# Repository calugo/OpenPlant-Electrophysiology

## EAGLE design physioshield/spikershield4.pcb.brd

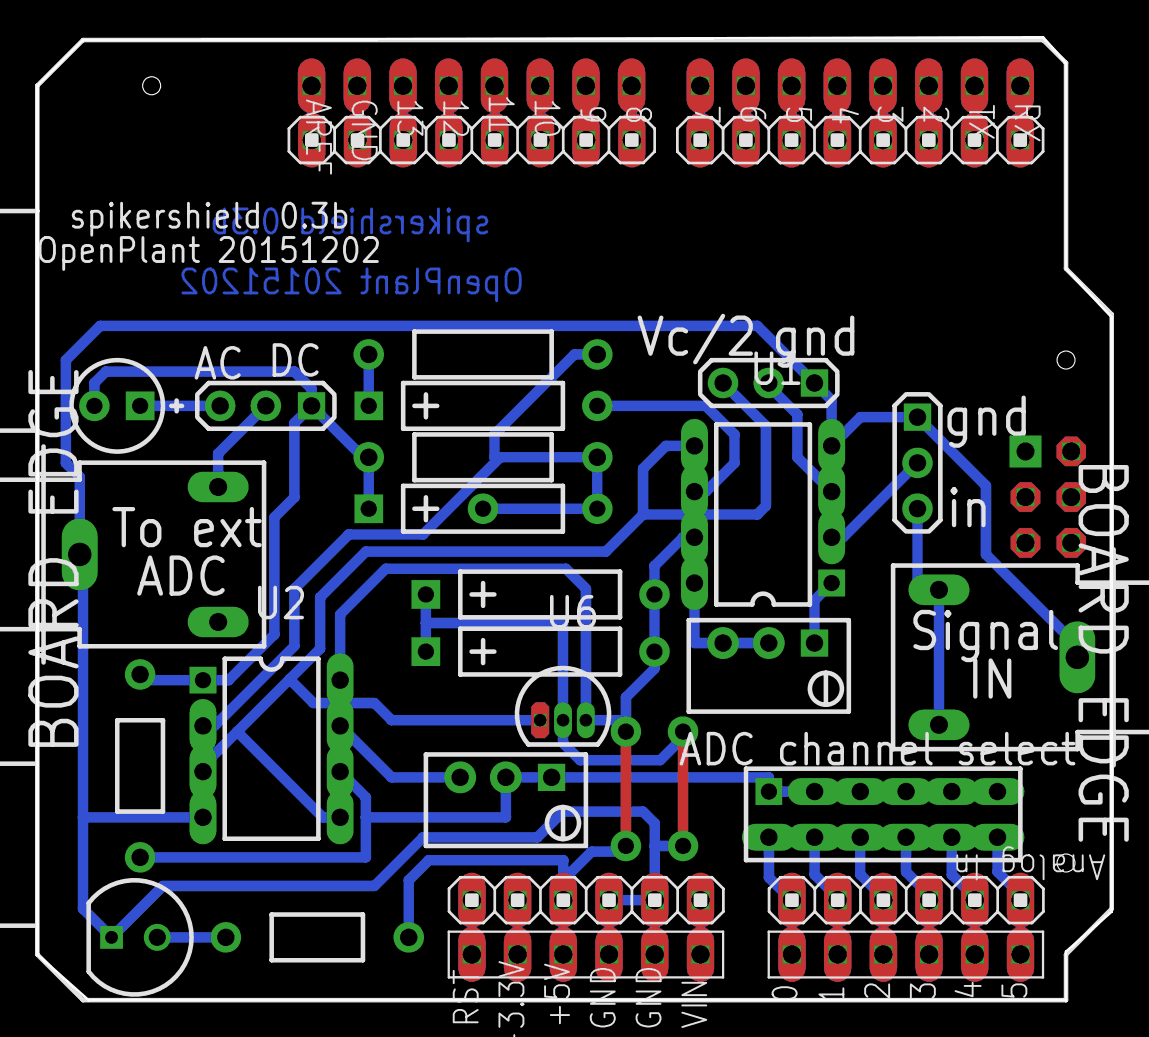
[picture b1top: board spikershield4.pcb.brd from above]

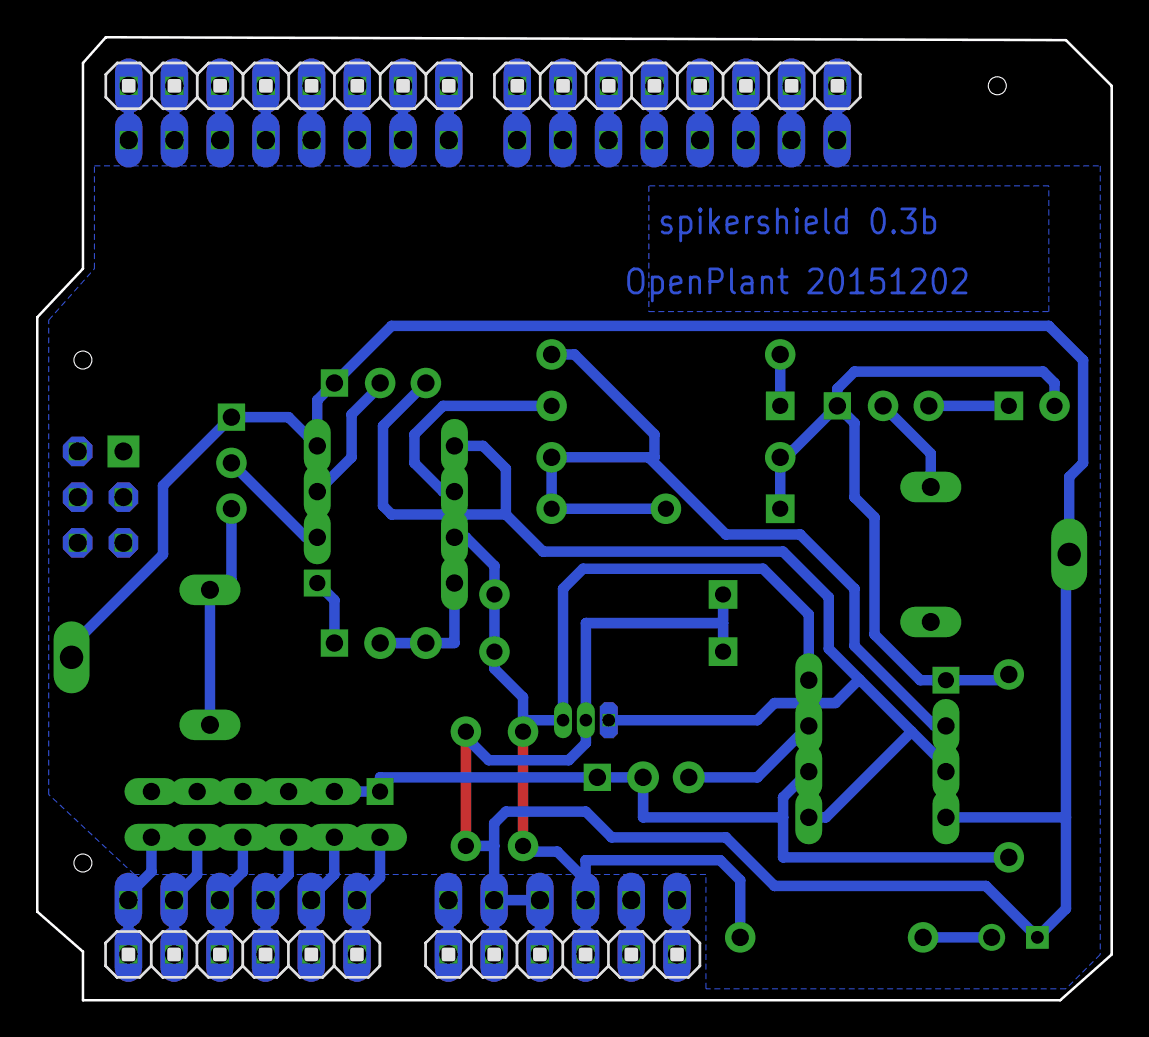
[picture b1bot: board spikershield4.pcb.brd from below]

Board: 2 copper layers, 59.7 x 53.5 mm, 43 parts (8 on the bottom side), 41 nets.

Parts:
C3: 10uF; CAP500AP_0PRIMARY
C4: 360pF; CAP500AP_0PRIMARY
C5: CAP100RP_1PRIMARY
C6: 1uF; CAP500AP_0PRIMARY
C7: 10nF; CAP500AP_0PRIMARY
D1: LED_2PRIMARY
HOLE1: COMP_3PRIMARY
HOLE2: COMP_4PRIMARY
HOLE3: COMP_5PRIMARY
J1, J6, J7, J12: 1X08_6PRIMARY
J2, J5, J11: JUMPER_3_7PRIMARY
J3, J4: RCA_JACK_8PRIMARY
J8, J9, J13: 1X06_9PRIMARY
PAD1: COMP_10PRIMARY
PAD2: COMP_11PRIMARY
PAD3: COMP_12PRIMARY
PAD4: COMP_13PRIMARY
PAD5: COMP_14PRIMARY
PAD6: COMP_15PRIMARY
PAD19, PAD20, PAD21, PAD22, PAD23: PAD_16PRIMARY
POWER1: 1X06_17PRIMARY
R1: POT3T_18PRIMARY
R2: 390; RES400_19PRIMARY
R5: 2.2M; RES500_20PRIMARY
R6: 100k; RES500_21PRIMARY
R7: 1k; RES400_19PRIMARY
R8: 5k; POT3T_18PRIMARY
U1: AD623AN_22PRIMARY
U2: AD623AN_23PRIMARY
U4: HDR-2X6_24PRIMARY
U6: TLE2426*LP_25PRIMARY

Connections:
NET_0: C6.2, C7.2, D1.2, J2.1, J3.1, J4.1, J5.1, J9.2, J9.3, PAD21.1, PAD22.1, POWER1.4, POWER1.5, U1.4, U2.4, U6.2
NET_1: J2.2, U1.3
NET_2: D1.1, R2.2
NET_3: J2.3, U1.5, U2.3, U2.5, U6.1
NET_4: R1.1, R1.2, R1.3, U1.1, U1.8
NET_5: R8.3, U2.7
NET_6: R7.1, R8.1, R8.2, U2.6, U4.1, U4.3, U4.5, U4.7, U4.9, U4.11
NET_7: J3.2, J3.3, J5.3
NET_8: J5.2, U1.2
NET_9: C3.1, U1.6
NET_10: C6.1, C7.1, J9.4, PAD19.1, PAD20.1, POWER1.3, R2.1, U1.7, U2.8, U6.3
NET_11: C4.1, PAD23.1, R5.1, R6.1, U2.2
NET_12: J1.6, J12.3
NET_13: J8.6, J13.1, U4.2
NET_14: J6.2, J7.7
NET_15: J8.5, J13.2, U4.4
NET_16: J8.4, J13.3, U4.6
NET_17: J8.3, J13.4, U4.8
NET_18: J8.2, J13.5, U4.10
NET_19: J9.6, POWER1.1
NET_20: J9.5, POWER1.2
NET_21: J9.1, POWER1.6
NET_22: J8.1, J13.6, U4.12
NET_23: J4.2, J11.2
NET_24: C4.2, C5.2, J11.1, R5.2, R7.2, U2.1
NET_25: J1.8, J12.1
NET_26: J1.7, J12.2
NET_27: C3.2, R6.2
NET_28: J1.5, J12.4
NET_29: J1.4, J12.5
NET_30: J1.3, J12.6
NET_31: J1.2, J12.7
NET_32: J1.1, J12.8
NET_33: J6.8, J7.1
NET_34: J6.7, J7.2
NET_35: J6.6, J7.3
NET_36: J6.5, J7.4
NET_37: J6.4, J7.5
NET_38: J6.3, J7.6
NET_39: C5.1, J11.3
NET_40: J6.1, J7.8

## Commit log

2016-04-23 OpenPlantRep
2016-05-10 Octopress init
2016-05-10 Site updated at 2016-05-10 01:56:22 UTC
2016-05-10 Site updated at 2016-05-10 02:11:50 UTC
2016-05-10 Site updated at 2016-05-10 02:36:09 UTC
2016-05-10 Site updated at 2016-05-10 02:48:09 UTC
2016-05-10 Site updated at 2016-05-10 03:03:58 UTC
2016-05-10 Site updated at 2016-05-10 03:08:27 UTC
2016-05-10 Site updated at 2016-05-10 03:09:11 UTC
2016-05-10 Site updated at 2016-05-10 03:11:01 UTC
2016-05-10 Site updated at 2016-05-10 03:13:34 UTC
2016-05-10 Site updated at 2016-05-10 03:14:57 UTC
2016-05-10 Site updated at 2016-05-10 09:36:06 UTC
2016-05-10 lorenz add
2016-05-10 Site updated at 2016-05-10 21:52:58 UTC
2016-05-10 Site updated at 2016-05-10 21:57:38 UTC
2017-01-16 Playstation2 controller for three motors
    Allows to use a Playstation 2 controller to control three stepper
    motors. Used to control the x,y,z, axis of the micromanipulator.
2017-01-16 minimal change, to test Github system
    No functional changes. TODO introduce delay in stepsize controls and see
    if it works better (now need to press another control before a further
    change in stepsize is allowed).
2017-02-14 Site updated at 2017-02-14 04:15:48 UTC
2017-02-14 Site updated at 2017-02-14 04:46:56 UTC
2017-02-14 test
2017-02-14 Site updated at 2017-02-14 04:57:39 UTC
2017-02-14 Site updated at 2017-02-14 05:09:57 UTC
2017-02-14 Site updated at 2017-02-14 05:13:23 UTC
2017-02-14 Site updated at 2017-02-14 05:31:54 UTC
2017-02-14 Site updated at 2017-02-14 05:33:24 UTC
2017-02-14 Site updated at 2017-02-14 05:40:42 UTC
2017-02-14 Site updated at 2017-02-14 05:42:19 UTC
2017-02-14 Site updated at 2017-02-14 05:44:29 UTC
2017-02-14 Site updated at 2017-02-14 05:46:47 UTC
2017-02-14 Site updated at 2017-02-14 05:49:13 UTC
2017-02-14 Site updated at 2017-02-14 05:52:55 UTC
2017-02-14 Site updated at 2017-02-14 05:56:26 UTC
2017-02-14 Site updated at 2017-02-14 06:10:15 UTC
2017-02-14 Site updated at 2017-02-14 06:16:32 UTC
2017-02-14 Site updated at 2017-02-14 07:42:41 UTC
2017-02-14 Site updated at 2017-02-14 07:44:44 UTC
2017-02-14 Site updated at 2017-02-14 07:46:56 UTC
2017-02-14 Site updated at 2017-02-14 07:48:56 UTC
2017-02-14 Site updated at 2017-02-14 07:50:29 UTC
2017-02-14 Site updated at 2017-02-14 07:51:40 UTC
2017-02-14 Site updated at 2017-02-14 07:54:22 UTC
2017-02-14 Site updated at 2017-02-14 07:56:48 UTC
2017-02-14 Site updated at 2017-02-14 08:02:03 UTC
2017-02-14 Site updated at 2017-02-14 08:04:37 UTC
2017-02-14 Site updated at 2017-02-14 08:07:48 UTC
2017-02-14 Site updated at 2017-02-14 08:09:38 UTC
2017-02-14 Site updated at 2017-02-14 08:11:28 UTC
2017-02-14 Site updated at 2017-02-14 08:14:09 UTC
2017-02-14 Site updated at 2017-02-14 08:15:57 UTC
2017-02-14 Site updated at 2017-02-14 08:17:51 UTC
2017-02-14 Site updated at 2017-02-14 08:20:51 UTC
2017-02-14 Site updated at 2017-02-14 08:22:36 UTC
2017-02-14 Site updated at 2017-02-14 08:24:42 UTC
2017-02-14 Site updated at 2017-02-14 08:26:59 UTC
2017-02-14 Site updated at 2017-02-14 08:32:51 UTC
2017-02-14 Site updated at 2017-02-14 08:34:17 UTC
2017-02-14 Site updated at 2017-02-14 08:35:54 UTC
2017-02-14 Site updated at 2017-02-14 08:37:19 UTC
2017-02-14 Site updated at 2017-02-14 13:37:14 UTC
2017-02-14 Site updated at 2017-02-14 13:41:53 UTC
2017-02-14 Site updated at 2017-02-14 15:05:26 UTC
2017-02-14 Site updated at 2017-02-14 15:06:19 UTC
2017-02-14 Site updated at 2017-02-14 16:40:05 UTC
2017-02-15 Site updated at 2017-02-15 03:42:53 UTC
2017-02-15 Site updated at 2017-02-15 03:44:30 UTC
2017-02-15 Site updated at 2017-02-15 03:46:16 UTC
2017-02-15 Site updated at 2017-02-15 03:47:54 UTC
2017-02-15 Site updated at 2017-02-15 03:56:43 UTC
2017-02-15 Site updated at 2017-02-15 03:58:04 UTC
2017-02-15 Site updated at 2017-02-15 04:00:51 UTC
2017-02-15 Site updated at 2017-02-15 04:07:28 UTC
2017-02-15 Site updated at 2017-02-15 04:14:56 UTC
2017-02-15 Site updated at 2017-02-15 04:44:24 UTC
2017-02-15 Site updated at 2017-02-15 04:47:06 UTC
2017-02-15 Site updated at 2017-02-15 14:10:15 UTC
2017-02-15 Site updated at 2017-02-15 14:12:56 UTC
2017-02-15 Site updated at 2017-02-15 14:20:26 UTC
2017-02-15 Site updated at 2017-02-15 14:39:18 UTC
2017-02-15 Site updated at 2017-02-15 14:40:04 UTC
2017-02-15 Site updated at 2017-02-15 14:46:02 UTC
2017-02-15 Site updated at 2017-02-15 14:52:25 UTC
2017-02-15 Site updated at 2017-02-15 14:56:26 UTC
2017-02-15 Site updated at 2017-02-15 14:58:45 UTC
2017-02-15 Site updated at 2017-02-15 14:59:58 UTC
2017-02-15 Site updated at 2017-02-15 15:02:15 UTC
2017-02-15 Site updated at 2017-02-15 15:04:27 UTC
2017-02-15 Site updated at 2017-02-15 15:05:49 UTC
2017-02-15 Site updated at 2017-02-15 23:21:21 UTC
2017-02-15 Site updated at 2017-02-15 23:23:53 UTC
2017-02-15 Site updated at 2017-02-15 23:26:04 UTC
2017-02-15 Site updated at 2017-02-15 23:33:58 UTC
2017-02-15 Site updated at 2017-02-15 23:42:59 UTC
2017-02-15 Site updated at 2017-02-15 23:46:17 UTC
2017-02-15 Site updated at 2017-02-15 23:51:36 UTC
2017-02-15 Site updated at 2017-02-15 23:52:30 UTC
2017-02-16 Site updated at 2017-02-16 00:15:22 UTC
2017-02-16 Site updated at 2017-02-16 00:21:45 UTC
2017-02-16 Site updated at 2017-02-16 00:32:09 UTC
2017-02-16 Site updated at 2017-02-16 00:36:41 UTC
2017-02-16 Site updated at 2017-02-16 00:44:48 UTC
2017-02-16 Site updated at 2017-02-16 00:49:31 UTC
2017-02-16 Site updated at 2017-02-16 00:57:52 UTC
2017-02-16 Site updated at 2017-02-16 01:00:37 UTC
2017-02-16 Site updated at 2017-02-16 01:04:52 UTC
2017-02-16 Site updated at 2017-02-16 01:21:44 UTC
2017-02-16 Site updated at 2017-02-16 01:28:42 UTC
2017-02-16 Site updated at 2017-02-16 01:59:53 UTC
2017-02-16 Site updated at 2017-02-16 02:06:13 UTC
2017-02-16 Site updated at 2017-02-16 02:21:30 UTC
2017-02-16 Site updated at 2017-02-16 02:27:32 UTC
2017-02-16 Site updated at 2017-02-16 02:29:40 UTC
2017-02-16 Site updated at 2017-02-16 02:32:20 UTC
2017-02-16 Site updated at 2017-02-16 02:33:46 UTC
2017-02-16 Site updated at 2017-02-16 02:35:51 UTC
2017-02-16 Site updated at 2017-02-16 02:39:09 UTC
2017-02-16 Site updated at 2017-02-16 02:40:51 UTC
2017-02-16 Site updated at 2017-02-16 02:42:15 UTC
2017-02-16 Site updated at 2017-02-16 02:44:19 UTC
2017-02-16 Site updated at 2017-02-16 02:49:14 UTC
2017-02-16 Site updated at 2017-02-16 02:56:32 UTC
2017-02-16 Site updated at 2017-02-16 02:58:37 UTC
2017-02-16 Site updated at 2017-02-16 03:21:23 UTC
2017-02-16 Site updated at 2017-02-16 03:27:40 UTC
2017-02-16 Site updated at 2017-02-16 03:32:08 UTC
2017-02-16 Site updated at 2017-02-16 03:37:08 UTC
2017-02-16 Site updated at 2017-02-16 03:44:01 UTC
2017-02-16 Site updated at 2017-02-16 03:45:20 UTC
2017-03-02 Site updated at 2017-03-02 00:22:20 UTC
2017-03-14 Site updated at 2017-03-14 18:26:22 UTC
2017-03-14 Site updated at 2017-03-14 18:29:03 UTC
2017-03-14 Site updated at 2017-03-14 22:36:50 UTC
2017-03-14 Site updated at 2017-03-14 22:56:49 UTC
2017-03-14 Site updated at 2017-03-14 22:57:59 UTC
2017-03-14 Site updated at 2017-03-14 23:16:44 UTC
2017-03-14 Site updated at 2017-03-14 23:20:42 UTC
2017-03-14 Site updated at 2017-03-14 23:24:08 UTC
2017-03-14 Site updated at 2017-03-14 23:26:44 UTC
2017-03-14 Site updated at 2017-03-14 23:28:40 UTC
2017-03-14 Site updated at 2017-03-14 23:34:00 UTC
2017-03-14 Site updated at 2017-03-14 23:35:39 UTC
2017-03-14 Site updated at 2017-03-14 23:40:36 UTC
2017-03-14 Site updated at 2017-03-14 23:43:19 UTC
2017-03-14 Site updated at 2017-03-14 23:46:42 UTC
2017-03-14 Site updated at 2017-03-14 23:54:48 UTC
2017-03-14 Site updated at 2017-03-14 23:59:57 UTC
2017-03-15 Site updated at 2017-03-15 00:04:44 UTC
2017-03-15 Site updated at 2017-03-15 00:07:22 UTC
2017-03-15 Site updated at 2017-03-15 00:14:31 UTC
2017-03-15 Site updated at 2017-03-15 00:19:35 UTC
2017-03-15 Site updated at 2017-03-15 00:49:21 UTC
2017-03-15 Site updated at 2017-03-15 01:05:13 UTC
2017-03-15 Site updated at 2017-03-15 01:13:12 UTC
2017-03-15 Site updated at 2017-03-15 01:17:25 UTC
2017-03-15 Site updated at 2017-03-15 01:41:14 UTC
2017-03-15 Site updated at 2017-03-15 01:43:43 UTC
2017-03-15 Site updated at 2017-03-15 01:49:43 UTC
2017-03-15 Site updated at 2017-03-15 02:03:05 UTC
2017-03-15 Site updated at 2017-03-15 15:57:09 UTC
2017-03-15 Site updated at 2017-03-15 16:32:46 UTC
2017-03-15 Site updated at 2017-03-15 17:33:16 UTC
2017-03-15 Site updated at 2017-03-15 17:52:07 UTC
2017-03-15 Site updated at 2017-03-15 18:17:04 UTC
2017-03-15 Site updated at 2017-03-15 18:19:05 UTC
2017-03-15 Site updated at 2017-03-15 18:21:32 UTC
2017-03-15 Site updated at 2017-03-15 18:24:10 UTC
2017-03-15 Site updated at 2017-03-15 18:27:01 UTC
2017-03-15 Site updated at 2017-03-15 19:47:08 UTC
2017-03-15 Site updated at 2017-03-15 19:51:37 UTC
2017-03-15 Site updated at 2017-03-15 21:07:46 UTC
2017-03-15 Site updated at 2017-03-15 22:42:23 UTC
2017-03-15 Site updated at 2017-03-15 22:47:10 UTC
2017-03-15 Site updated at 2017-03-15 22:51:19 UTC
2017-03-15 Site updated at 2017-03-15 22:53:45 UTC
2017-03-15 Site updated at 2017-03-15 23:00:12 UTC
2017-03-15 Site updated at 2017-03-15 23:02:34 UTC
2017-03-15 Site updated at 2017-03-15 23:15:59 UTC
2017-03-15 Site updated at 2017-03-15 23:19:03 UTC
2017-03-15 Site updated at 2017-03-15 23:24:32 UTC
2017-03-15 Site updated at 2017-03-15 23:34:22 UTC
2017-03-15 Site updated at 2017-03-15 23:36:36 UTC
2017-03-15 Site updated at 2017-03-15 23:39:02 UTC
2017-03-15 Site updated at 2017-03-15 23:41:06 UTC
2017-03-16 Site updated at 2017-03-16 00:17:25 UTC
2017-03-16 Site updated at 2017-03-16 09:44:17 UTC
2017-03-16 Site updated at 2017-03-16 09:57:58 UTC
2017-03-16 Site updated at 2017-03-16 10:14:18 UTC
2017-03-16 Site updated at 2017-03-16 11:19:08 UTC
2017-03-16 Site updated at 2017-03-16 13:40:12 UTC
2017-03-16 Site updated at 2017-03-16 13:43:47 UTC
2017-03-16 Site updated at 2017-03-16 19:27:31 UTC
2017-03-16 Site updated at 2017-03-16 19:31:15 UTC
2017-03-16 Site updated at 2017-03-16 21:14:04 UTC
2017-03-16 Site updated at 2017-03-16 21:16:55 UTC
2017-03-17 Site updated at 2017-03-17 00:21:59 UTC
2017-03-17 Site updated at 2017-03-17 00:28:09 UTC
2017-03-17 Site updated at 2017-03-17 00:32:03 UTC
2017-03-17 Site updated at 2017-03-17 00:38:54 UTC
2017-03-17 Site updated at 2017-03-17 00:43:46 UTC
2017-03-17 Site updated at 2017-03-17 00:48:31 UTC
2017-03-17 Site updated at 2017-03-17 00:50:09 UTC
2017-03-17 Site updated at 2017-03-17 00:52:37 UTC
2017-03-17 Site updated at 2017-03-17 00:55:58 UTC
2017-03-17 Site updated at 2017-03-17 01:28:33 UTC
2017-03-17 Site updated at 2017-03-17 01:46:14 UTC
2017-03-17 Site updated at 2017-03-17 01:47:26 UTC
2017-03-17 Site updated at 2017-03-17 01:54:43 UTC
2017-03-17 Site updated at 2017-03-17 02:17:39 UTC
2017-03-17 Site updated at 2017-03-17 02:44:44 UTC
2017-03-17 Site updated at 2017-03-17 02:47:27 UTC
2017-03-17 Site updated at 2017-03-17 02:49:25 UTC
2017-03-17 Site updated at 2017-03-17 02:51:32 UTC
2017-03-17 Site updated at 2017-03-17 02:54:02 UTC
2017-03-17 Site updated at 2017-03-17 02:57:11 UTC
2017-03-17 Site updated at 2017-03-17 03:02:50 UTC
2017-03-17 Site updated at 2017-03-17 03:18:55 UTC
2017-03-17 Site updated at 2017-03-17 03:28:28 UTC
2017-03-17 Site updated at 2017-03-17 03:32:19 UTC
2017-03-17 Site updated at 2017-03-17 03:35:36 UTC
2017-03-19 Site updated at 2017-03-19 11:41:41 UTC
2017-03-19 Site updated at 2017-03-19 11:44:44 UTC
2017-03-19 Site updated at 2017-03-19 11:46:53 UTC
2017-03-21 Site updated at 2017-03-21 17:42:49 UTC
